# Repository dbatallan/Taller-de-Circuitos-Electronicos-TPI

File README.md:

# Taller-de-Circuitos-Electronicos-TPI

## Integrantes del Grupo

| Alumno | Padrón |
| -- | -- |
| BATALLAN, David Leonardo | 97529 |
| CARICATO, Ezequiel Nicolas | 93966 |

## Fechas

- **CHECKPOINT 1 - 04/04/2025**:
  - DISEÑO VERIFICADO POR SIMULACIÓN DE LAZO DE TENSIÓN (ESTÁTICO).
  - SELECCIÓN DEL TRANSISTOR DE PASO.
  - DISEÑO VERIFICADO POR SIMULACIÓN DEL LAZO DE CORRIENTE (ESTÁTICO).
  - ESQUEMÁTICO DE PCB.
  - [Informe](https://www.overleaf.com/3897976553wqghxpknkzrb#0e6126)

- **CHECKPOINT 2 - 25/04/2025**:
  - DISEÑO VERIFICADO POR SIMULACIÓN DE LA COMPENSACIÓN DE LOS DOS LAZOS.
  - ANÁLISIS TÉRMICO.
  - DISEÑO DE PCB.
 
- **CHECKPOINT 3 - 09/05/2025**:
  - CARACTERIZACIÓN Y VALIDACIÓN DE REGULADOR LINEAL CON LAZO DE TENSIÓN Y CORRIENTE.

- **CHECKPOINT 4 - 30/05/2025**:
  - DISEÑO VERIFICADO POR SIMULACIÓN DE LA FUENTE BUCK A LAZO ABIERTO.
  - IMPLEMENTACIÓN DE CIRCUITO PWM (PCB).
  - CARACTERÍSTICAS FÍSICAS DEL INDUCTOR DISEÑADO.
  - DISEÑO PCB DE LA BUCK EN LAZO ABIERTO.

- **CHECKPOINT 5 - 27/06/2025**:
  - CARACTERIZACIÓN Y VALIDACIÓN DE REGULADOR CONMUTADO EN LAZO CERRADO CON IMPLEMENTACIÓN DE PWM.
  - DISEÑO DE PCB + CEM.

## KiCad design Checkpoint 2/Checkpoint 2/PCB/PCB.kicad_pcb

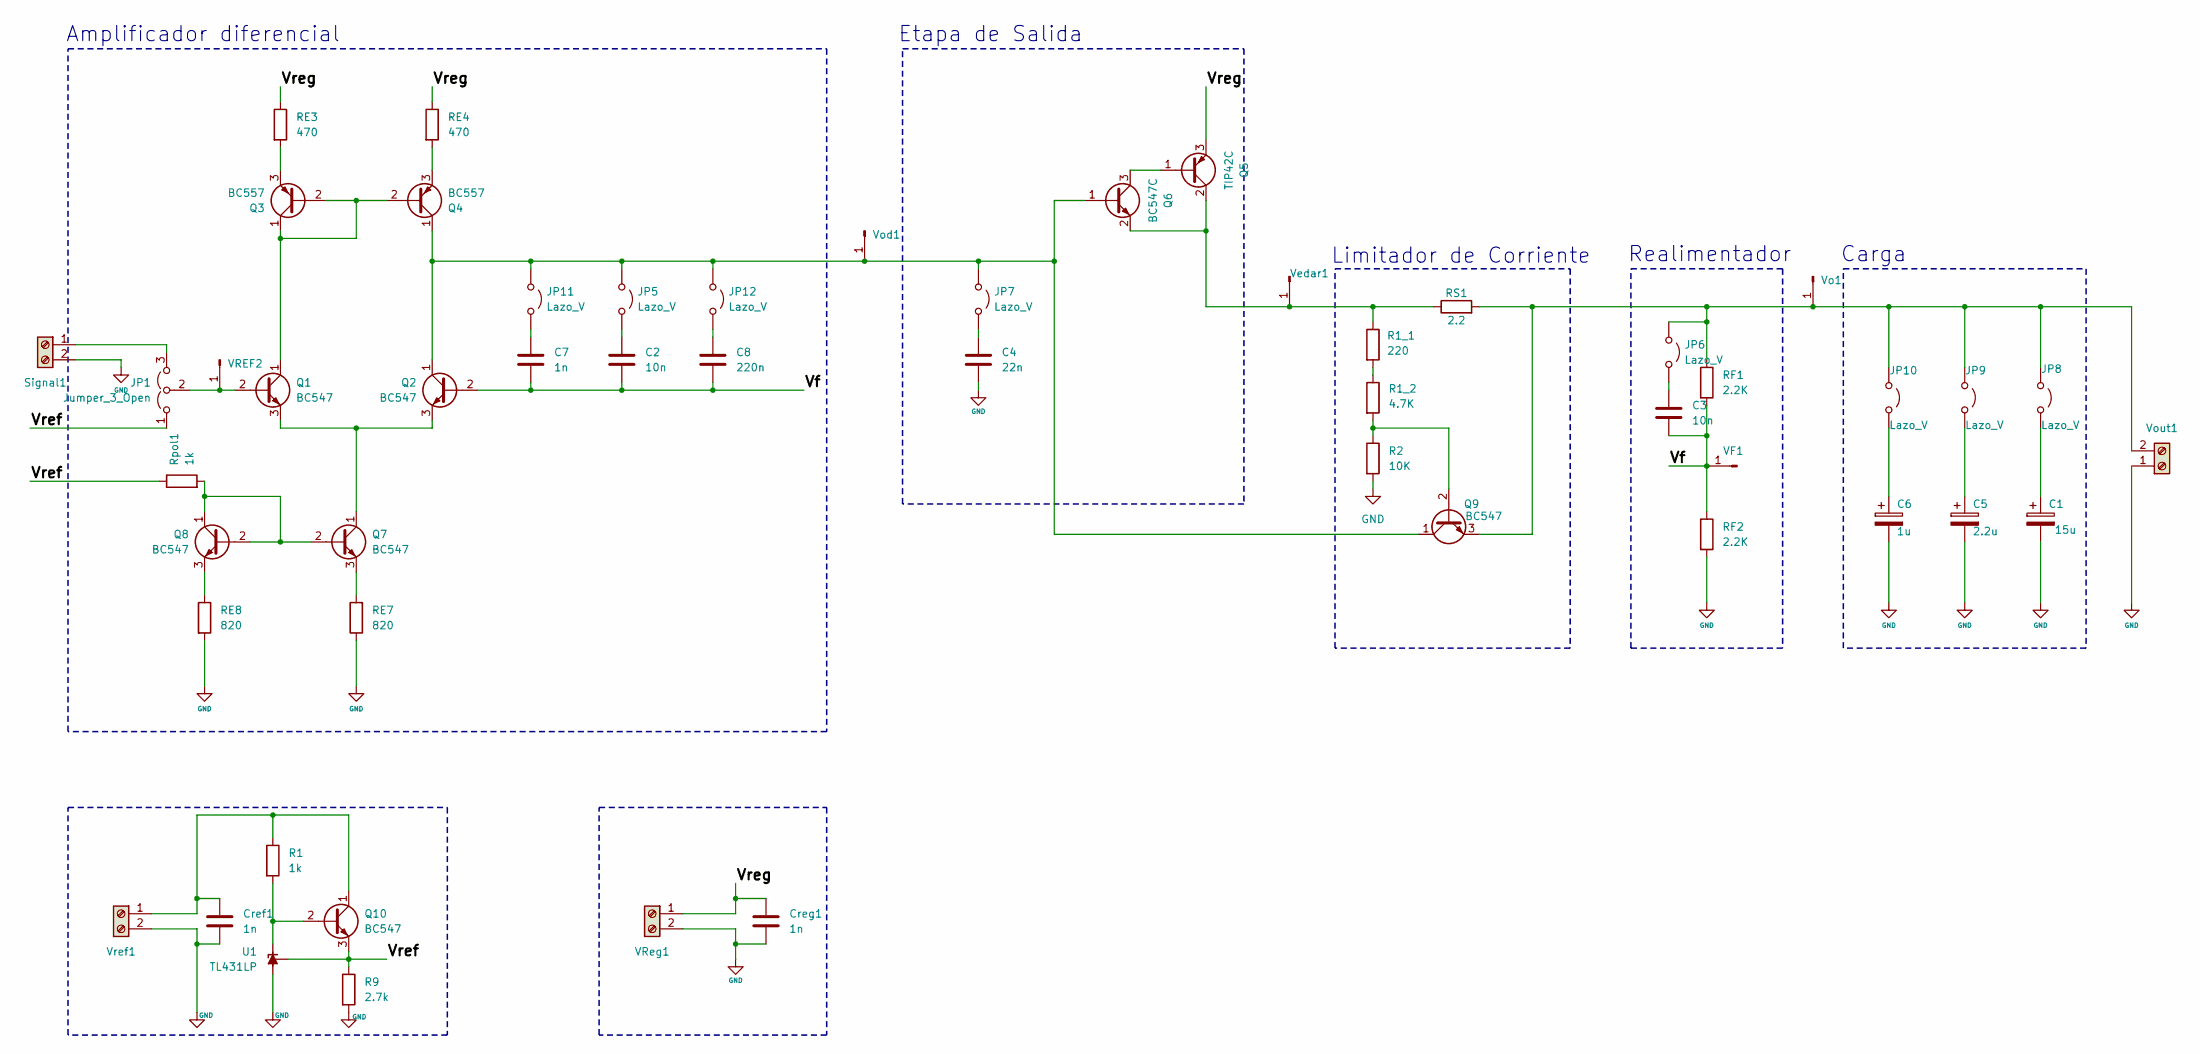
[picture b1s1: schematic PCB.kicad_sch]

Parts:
C1: 15u; Capacitor_electrolitico_22u_Radial_D6.3mm_P2.50mm
C2, C3: 10n; Capacitor_10nf_L7.2mm_W3.0mm_P5.00mm_FKS2_FKP2_MKS2_MKP2
C4: 22n; Capacitor_22nf_L7.2mm_W3.0mm_P5.00mm_FKS2_FKP2_MKS2_MKP2
C5: 2.2u; Capacitor_electrolitico_2.2u_Radial_D5.0mm_P2.00mm
C6: 1u; Capacitor_electrolitico_1u_Radial_D5.0mm_P2.00mm
C7: 1n; Capacitor_1nf_L7.2mm_W3.0mm_P5.00mm_FKS2_FKP2_MKS2_MKP2
C8: 220n; Capacitor_220n_Rect_L10.3mm_W7.2mm_P7.50mm_MKS4
Cref1: 1n; Capacitor_1nf_L7.2mm_W3.0mm_P5.00mm_FKS2_FKP2_MKS2_MKP2
Creg1: 1n; Capacitor_1nf_L7.2mm_W3.0mm_P5.00mm_FKS2_FKP2_MKS2_MKP2
JP1: Jumper_3_Open; PinHeader_1x03_P2.54mm_Vertical
JP5, JP6, JP7, JP8, JP9, JP10, JP11, JP12: Lazo_V; PinHeader_1x02_P2.54mm_Vertical
Q1, Q2, Q7, Q8, Q9, Q10: BC547
Q3, Q4: BC557
Q5: TIP42C; TIP42
Q6: BC547C; BC547
R1: 1k; Resistor_1_4W_L6.3mm_D2.5mm_P10.16mm_Horizontal
R1_1: 220; Resistor_1_4W_L6.3mm_D2.5mm_P10.16mm_Horizontal
R1_2: 4.7K; Resistor_1_4W_L6.3mm_D2.5mm_P10.16mm_Horizontal
R2: 10K; Resistor_1_4W_L6.3mm_D2.5mm_P10.16mm_Horizontal
R9: 2.7k; Resistor_1_4W_L6.3mm_D2.5mm_P10.16mm_Horizontal
RE3, RE4: 470; Resistor_1_4W_L6.3mm_D2.5mm_P10.16mm_Horizontal
RE7, RE8: 820; Resistor_1_4W_L6.3mm_D2.5mm_P10.16mm_Horizontal
RF1, RF2: 2.2K; Resistor_1_4W_L6.3mm_D2.5mm_P10.16mm_Horizontal
RS1: 2.2; R_Axial_Power_L38.0mm_W6.4mm_P40.64mm
Rpol1: 1k; Resistor_1_4W_L6.3mm_D2.5mm_P10.16mm_Horizontal
Signal1: Screw_Terminal_01x02; Terminal_MKDS-3-2-5.08_1x02_P5.08mm_Horizontal
U1: TL431LP; TL431
VF1: Conn_01x01_Pin; Pin_Vertical_1x01_P2.54mm_Vertical
VREF2: Conn_01x01_Pin; Pin_Vertical_1x01_P2.54mm_Vertical
VReg1: Screw_Terminal_01x02; Terminal_MKDS-3-2-5.08_1x02_P5.08mm_Horizontal
Vedar1: Conn_01x01_Pin; Pin_Vertical_1x01_P2.54mm_Vertical
Vo1: Conn_01x01_Pin; Pin_Vertical_1x01_P2.54mm_Vertical
Vod1: Conn_01x01_Pin; Pin_Vertical_1x01_P2.54mm_Vertical
Vout1: Screw_Terminal_01x02; Terminal_MKDS-3-2-5.08_1x02_P5.08mm_Horizontal
Vref1: Screw_Terminal_01x02; Terminal_MKDS-3-2-5.08_1x02_P5.08mm_Horizontal

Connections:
/Vf: C2.2, C3.2, C7.2, C8.2, Q2.2 (B), RF1.2, RF2.1, VF1.1
/Vref: JP1.1 (A), Q10.3 (E), R9.1, Rpol1.1, U1.1 (REF)
/Vreg: Creg1.1, Q5.3 (E), RE3.1, RE4.1, VReg1.1
GND: C1.2, C4.2, C5.2, C6.2, Cref1.2, Creg1.2, R2.2, R9.2, RE7.1, RE8.2, RF2.2, Signal1.2, U1.2 (A), VReg1.2, Vout1.1, Vref1.2
unnamed: JP1.3 (B), Signal1.1
unnamed: JP1.2 (C), Q1.2 (B), VREF2.1
unnamed: C2.1, JP5.1 (A)
unnamed: C3.1, JP6.1 (A)
unnamed: C4.1, JP7.1 (A)
unnamed: C1.1, JP8.1 (A)
unnamed: C5.1, JP9.1 (A)
unnamed: C6.1, JP10.1 (A)
unnamed: JP6.2 (B), JP8.2 (B), JP9.2 (B), JP10.2 (B), Q9.3 (E), RF1.1, RS1.2, Vo1.1, Vout1.2
unnamed: C7.1, JP11.1 (A)
unnamed: JP5.2 (B), JP7.2 (B), JP11.2 (B), JP12.2 (B), Q2.1 (C), Q4.1 (C), Q6.1 (B), Q9.1 (C), Vod1.1
unnamed: C8.1, JP12.1 (A)
unnamed: Q1.1 (C), Q3.1 (C), Q3.2 (B), Q4.2 (B)
unnamed: Q1.3 (E), Q2.3 (E), Q7.1 (C)
unnamed: Q3.3 (E), RE3.2
unnamed: Q4.3 (E), RE4.2
unnamed: Q5.1 (B), Q6.3 (C)
unnamed: Q5.2 (C), Q6.2 (E), R1_1.1, RS1.1, Vedar1.1
unnamed: Q7.2 (B), Q8.1 (C), Q8.2 (B), Rpol1.2
unnamed: Q7.3 (E), RE7.2
unnamed: Q8.3 (E), RE8.1
unnamed: Q9.2 (B), R1_2.2, R2.1
unnamed: Q10.2 (B), R1.2, U1.3 (K)
unnamed: Cref1.1, Q10.1 (C), R1.1, Vref1.1
unnamed: R1_1.2, R1_2.1

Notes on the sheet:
Limitador de Corriente
Carga
Realimentador
Etapa de Salida
Amplificador diferencial

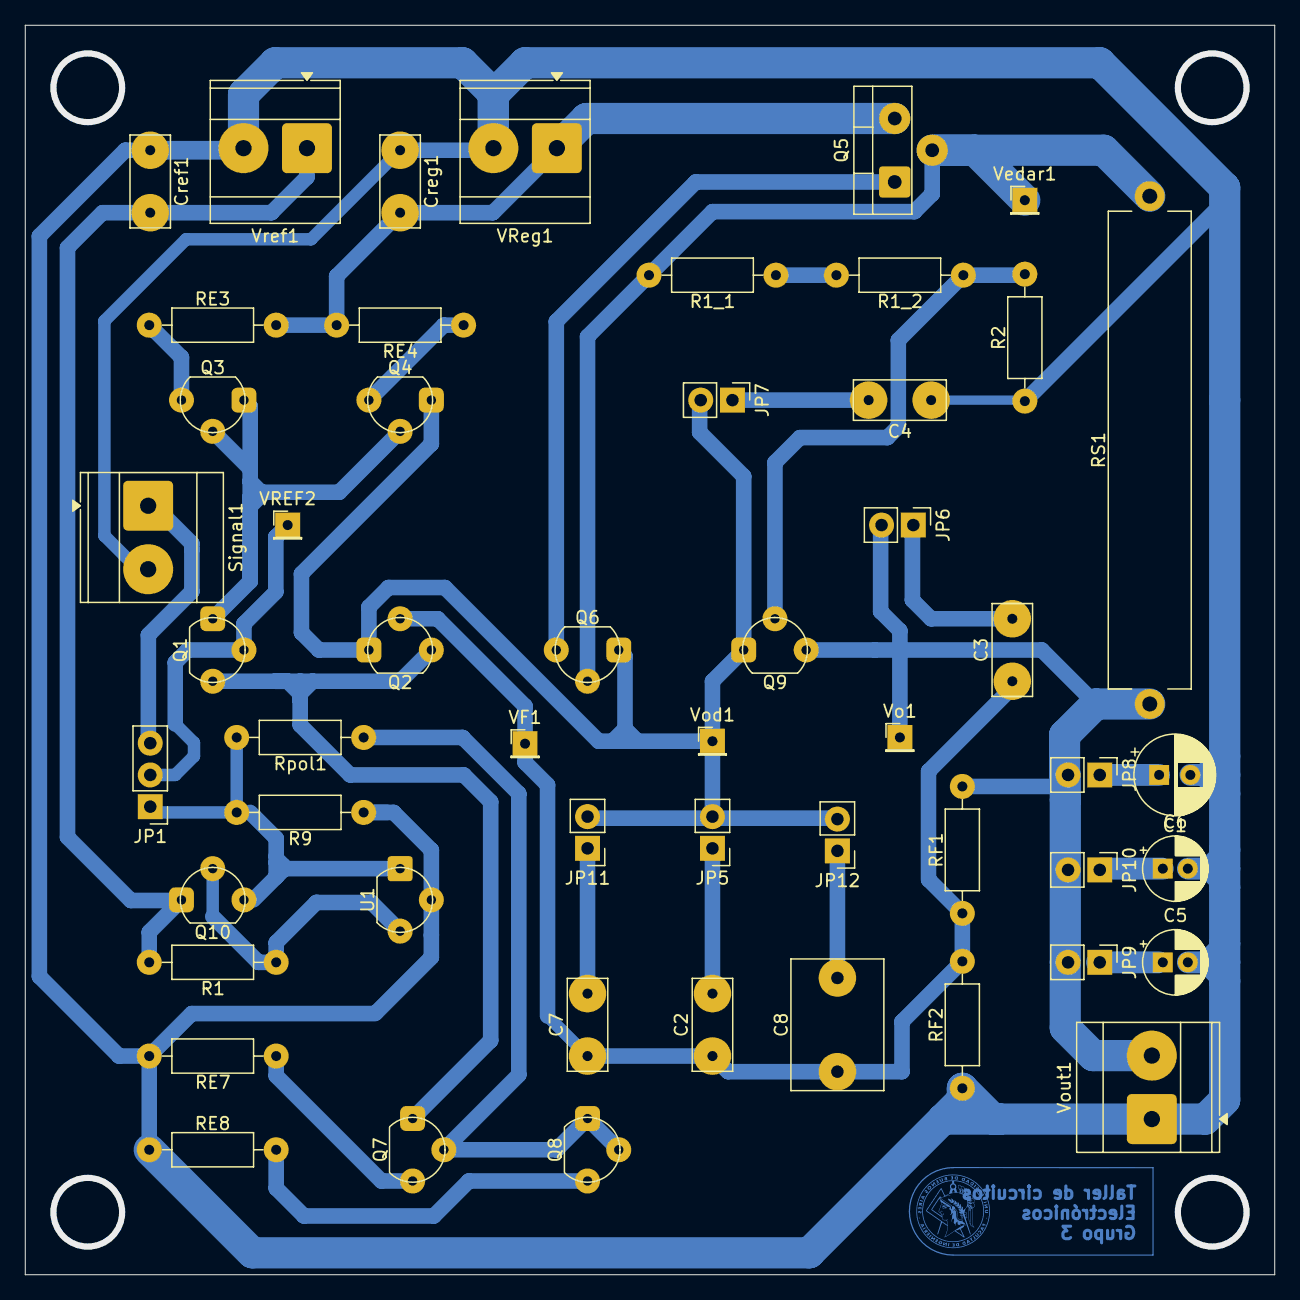
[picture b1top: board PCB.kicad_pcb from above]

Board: 2 copper layers, 100.0 x 100.0 mm, 52 parts (0 on the bottom side), 29 nets.

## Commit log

2025-03-24 Subo Carpeta Checkpoint 1
    Agregamos la Fuente de corriente y estamos definiendo la RE
2025-03-25 Limitador Fallback
    Agrego version 1.5
2025-03-27 limitador de Corriente
    Falta implementar el limitador de corriente
2025-03-28 Subo La version Funcionando
2025-03-28 Agregue el esquema de KiCad, no esta completo
2025-03-30 Agrego diseño en Orcad
    Con simulacion de PSpice
2025-03-30 Agrego Etapa de ganancia
    Agrego version 2.5
2025-03-30 Limitador de Correinte 2.5
    Actualizacion
2025-03-30 Cambio transistor de Paso
2025-03-31 Version Final CP1
2025-04-02 Actualizo Version Final
2025-04-02 Ganancia de LAzo
2025-04-25 Checkpoint 2
    Subo archivos
2025-05-08 Checkpoint 3
